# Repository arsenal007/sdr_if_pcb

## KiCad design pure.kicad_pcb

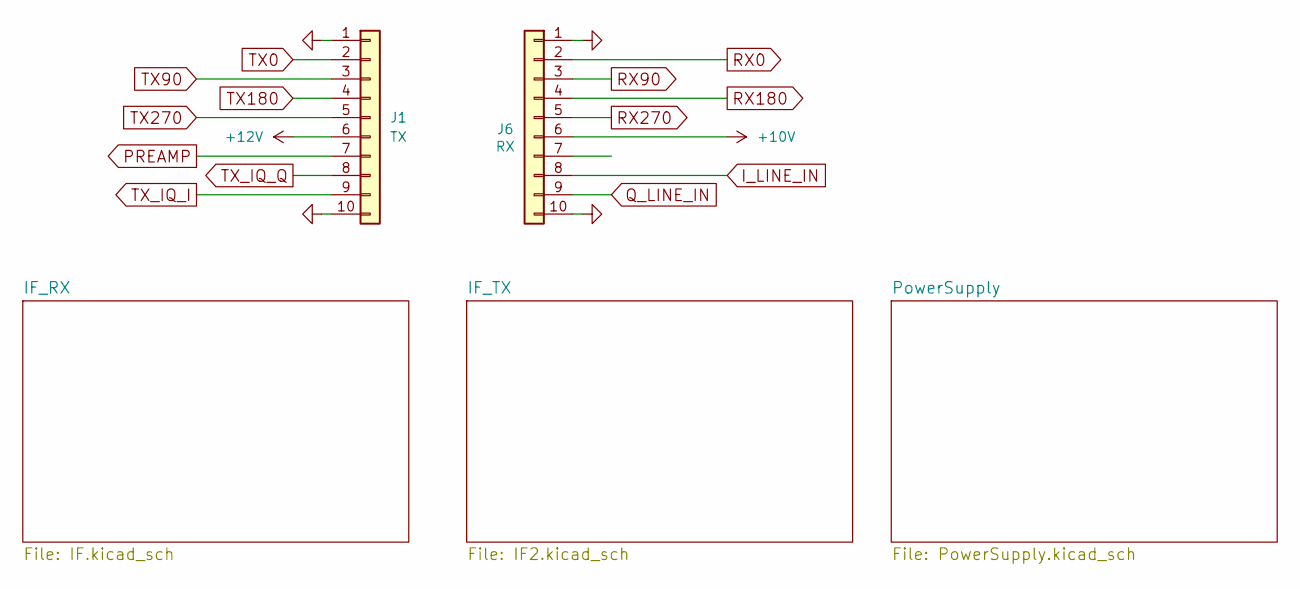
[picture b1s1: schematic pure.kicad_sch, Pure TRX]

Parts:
J1: TX; PinHeader_1x10_P2.54mm_Vertical
J6: RX; PinHeader_1x10_P2.54mm_Vertical

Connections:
+10V: J6.6; also elsewhere on the board
+12V: J1.6; also elsewhere on the board
GND: J1.1, J1.10, J6.1, J6.10; also elsewhere on the board
I_LINE_IN: J6.8; also elsewhere on the board
PREAMP: J1.7; also elsewhere on the board
Q_LINE_IN: J6.9; also elsewhere on the board
RX0: J6.2; also elsewhere on the board
RX90: J6.3; also elsewhere on the board
RX180: J6.4; also elsewhere on the board
RX270: J6.5; also elsewhere on the board
TX0: J1.2; also elsewhere on the board
TX90: J1.3; also elsewhere on the board
TX180: J1.4; also elsewhere on the board
TX270: J1.5; also elsewhere on the board
TX_IQ_I: J1.9; also elsewhere on the board
TX_IQ_Q: J1.8; also elsewhere on the board

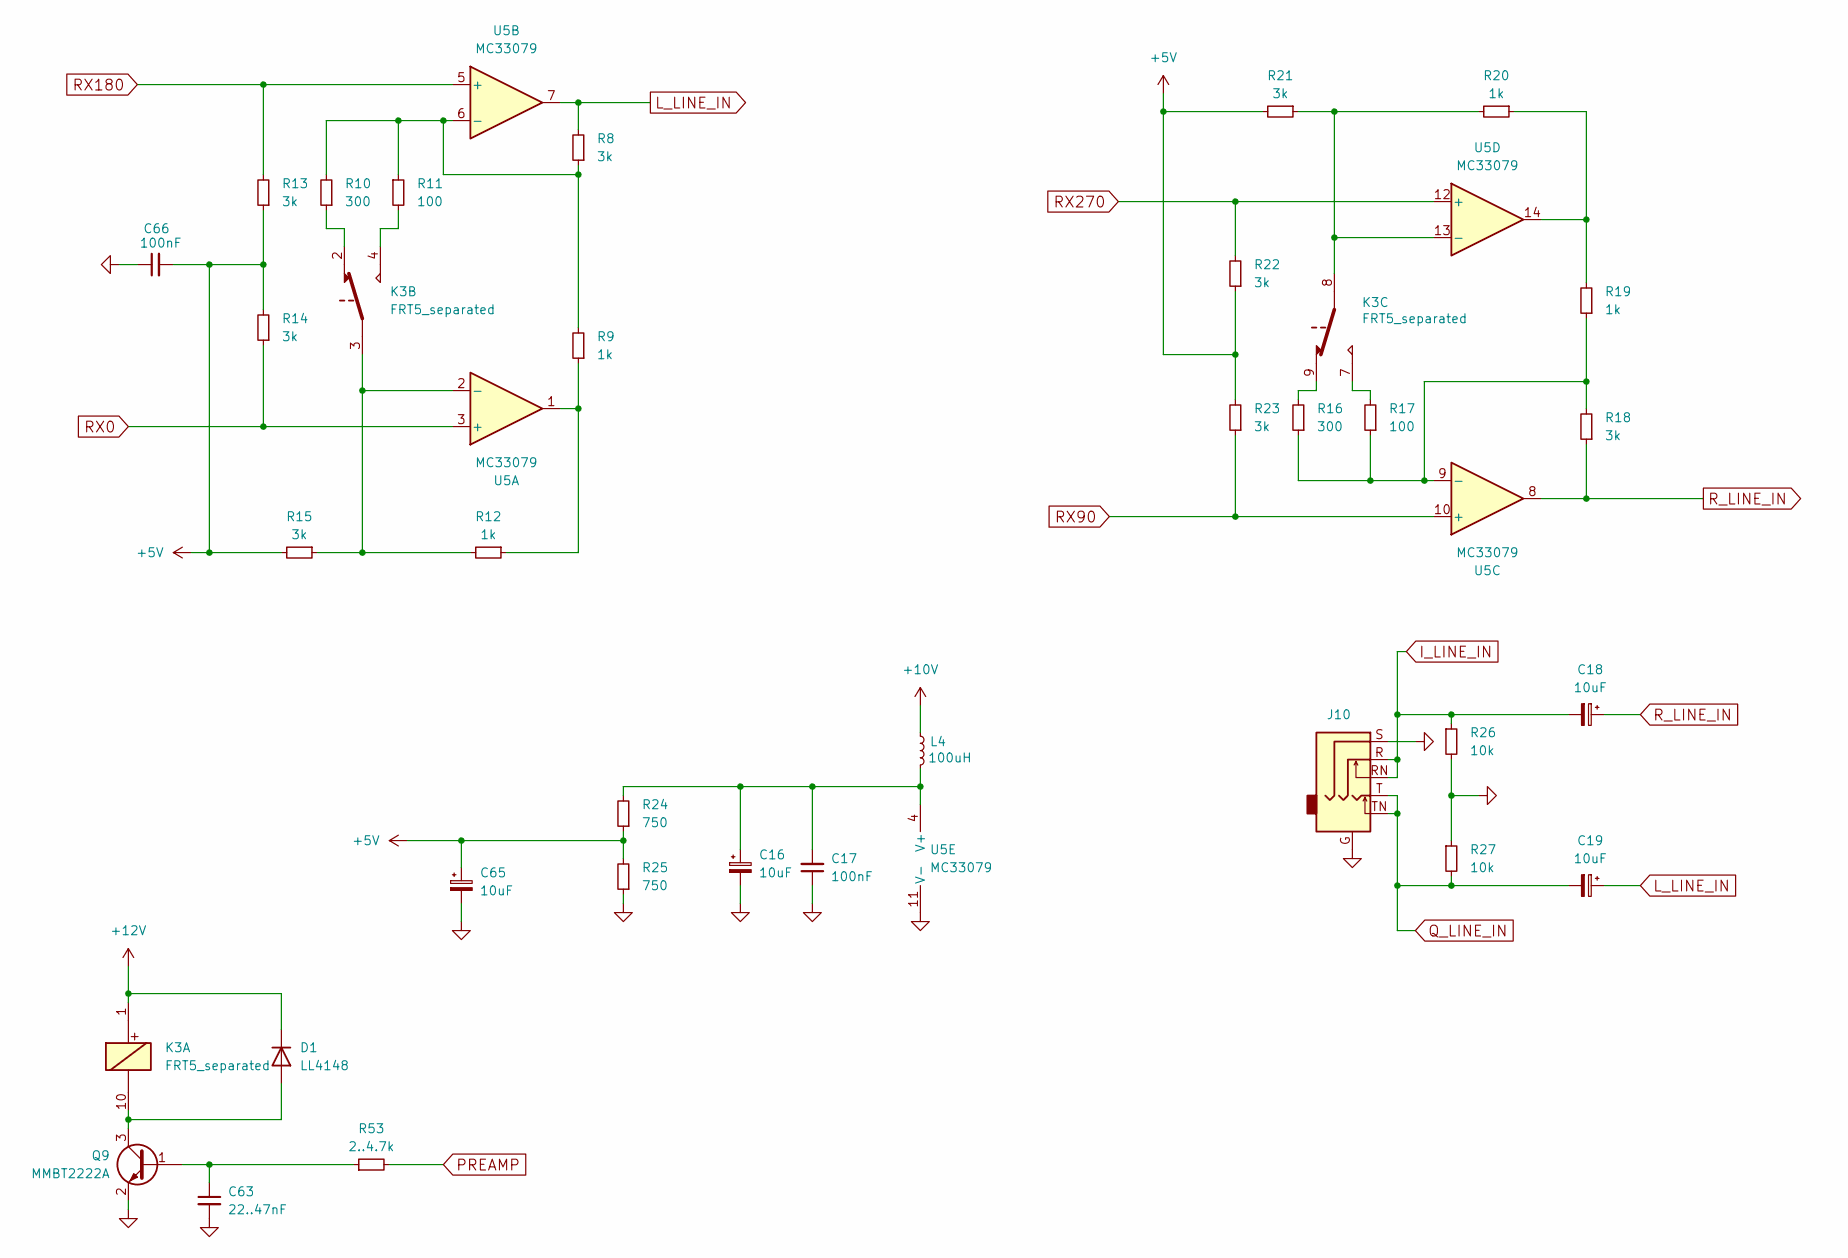
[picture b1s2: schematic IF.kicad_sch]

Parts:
C16, C18, C19, C65: 10uF; CP_EIA-3216-18_Kemet-A_Pad1.58x1.35mm_HandSolder; JLCPCB C123294
C17, C66: 100nF; C_1206_0603; JLCPCB C14663
C63: 22..47nF; C_1206_0603
D1: LL4148; D_MiniMELF
J10: AudioJack3_Ground_SwitchTR; Jack_3.5mm_CUI_SJ1-3525N_Horizontal
K3: FRT5_separated; Relay_DPDT_FRT5
L4: 100uH; L_Axial_L5.3mm_D2.2mm_P10.16mm_Horizontal_Vishay_IM-1; JLCPCB C394100
Q9: MMBT2222A; SOT-23
R8, R13, R14, R15, R18, R21, R22, R23: 3k; R_0603_1608Metric_Pad0.98x0.95mm_HandSolder; JLCPCB C4211
R9, R12, R19, R20: 1k; R_0603_1608Metric_Pad0.98x0.95mm_HandSolder; JLCPCB C21190
R10, R16: 300; R_0603_1608Metric_Pad0.98x0.95mm_HandSolder; JLCPCB C23025
R11, R17: 100; R_0603_1608Metric_Pad0.98x0.95mm_HandSolder; JLCPCB C22775
R24, R25: 750; R_1206_0603; JLCPCB C23241
R26, R27: 10k; R_0603_1608Metric_Pad0.98x0.95mm_HandSolder; JLCPCB C25804
R53: 2..4.7k; R_1206_0603
U5: MC33079; SOIC-14_3.9x8.7mm_P1.27mm

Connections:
+5V: C65.1, C66.2, R13.1, R14.2, R15.2, R21.2, R22.1, R23.2, R24.1, R25.2; also elsewhere on the board
+10V: L4.1; also elsewhere on the board
+12V: D1.1 (K), K3.1; also elsewhere on the board
GND: C16.2, C17.1, C63.2, C65.2, C66.1, J10.G, J10.S, Q9.2 (E), R25.1, R26.2, R27.1, U5.11 (V-); also elsewhere on the board
I_LINE_IN: C18.2, J10.R, J10.RN, R26.1; also elsewhere on the board
L_LINE_IN: C19.1, R8.2, U5.7
unnamed: D1.2 (A), K3.10, Q9.3 (C)
unnamed: K3.2, R10.1
unnamed: K3.4, R11.2
unnamed: K3.7, R17.2
unnamed: K3.9, R16.2
unnamed: C63.1, Q9.1 (B), R53.1
unnamed: R9.1, R12.1, U5.1
unnamed: R19.2, R20.1, U5.14
unnamed: K3.3, R12.2, R15.1, U5.2 (-)
unnamed: R8.1, R9.2, R10.2, R11.1, U5.6 (-)
unnamed: R16.1, R17.1, R18.2, R19.1, U5.9 (-)
unnamed: K3.8, R20.2, R21.1, U5.13 (-)
unnamed: C16.1, C17.2, L4.2, R24.2, U5.4 (V+)
PREAMP: R53.2; also elsewhere on the board
Q_LINE_IN: C19.2, J10.T, J10.TN, R27.2; also elsewhere on the board
RX0: R14.1, U5.3 (+); also elsewhere on the board
RX90: R23.1, U5.10 (+); also elsewhere on the board
RX180: R13.2, U5.5 (+); also elsewhere on the board
RX270: R22.2, U5.12 (+); also elsewhere on the board
R_LINE_IN: C18.1, R18.1, U5.8

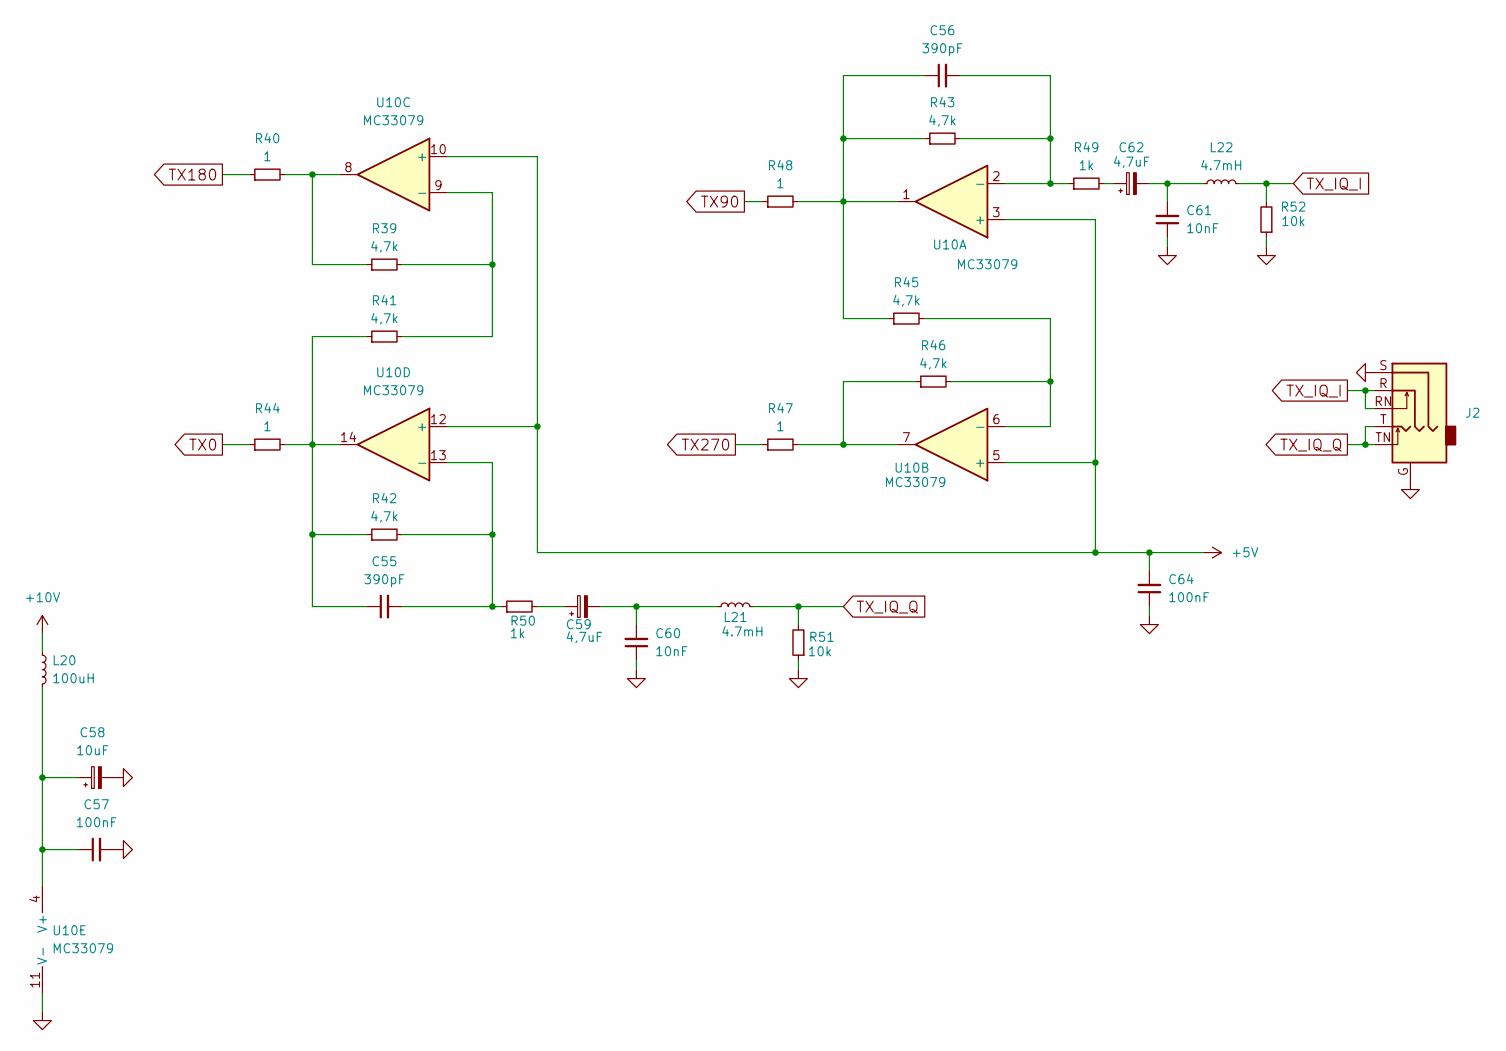
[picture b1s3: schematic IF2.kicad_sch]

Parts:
C55, C56: 390pF; C_0603_1608Metric_Pad1.08x0.95mm_HandSolder
C57, C64: 100nF; C_1206_0603
C58: 10uF; CP_EIA-3216-18_Kemet-A_Pad1.58x1.35mm_HandSolder
C59, C62: 4,7uF; CP_EIA-3216-18_Kemet-A_Pad1.58x1.35mm_HandSolder
C60, C61: 10nF; C_0603_1608Metric_Pad1.08x0.95mm_HandSolder
J2: AudioJack3_Ground_SwitchTR; Jack_3.5mm_CUI_SJ1-3525N_Horizontal
L20: 100uH; L_Axial_L5.3mm_D2.2mm_P10.16mm_Horizontal_Vishay_IM-1
L21, L22: 4.7mH; L_Axial_L5.3mm_D2.2mm_P10.16mm_Horizontal_Vishay_IM-1
R39, R41, R42, R43, R45, R46: 4,7k; R_0603_1608Metric_Pad0.98x0.95mm_HandSolder
R40, R44, R47, R48: 1; R_1206_0603
R49, R50: 1k; R_0603_1608Metric_Pad0.98x0.95mm_HandSolder
R51, R52: 10k; R_0603_1608Metric_Pad0.98x0.95mm_HandSolder
U10: MC33079; SOIC-14_3.9x8.7mm_P1.27mm

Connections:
+5V: C64.2, U10.3 (+), U10.5 (+), U10.10 (+), U10.12 (+); also elsewhere on the board
+10V: L20.1; also elsewhere on the board
GND: C57.2, C58.2, C60.1, C61.1, C64.1, J2.G, J2.S, R51.1, R52.1, U10.11 (V-); also elsewhere on the board
unnamed: C55.1, R41.1, R42.1, R44.2, U10.14
unnamed: C56.1, R43.1, R45.1, R48.2, U10.1
unnamed: C59.1, R50.2
unnamed: C59.2, C60.2, L21.1
unnamed: C61.2, C62.2, L22.1
unnamed: C62.1, R49.2
unnamed: R39.1, R40.2, U10.8
unnamed: R46.1, R47.2, U10.7
unnamed: C56.2, R43.2, R49.1, U10.2 (-)
unnamed: R45.2, R46.2, U10.6 (-)
unnamed: R39.2, R41.2, U10.9 (-)
unnamed: C55.2, R42.2, R50.1, U10.13 (-)
unnamed: C57.1, C58.1, L20.2, U10.4 (V+)
TX0: R44.1; also elsewhere on the board
TX90: R48.1; also elsewhere on the board
TX180: R40.1; also elsewhere on the board
TX270: R47.1; also elsewhere on the board
TX_IQ_I: J2.R, J2.RN, L22.2, R52.2; also elsewhere on the board
TX_IQ_Q: J2.T, J2.TN, L21.2, R51.2; also elsewhere on the board

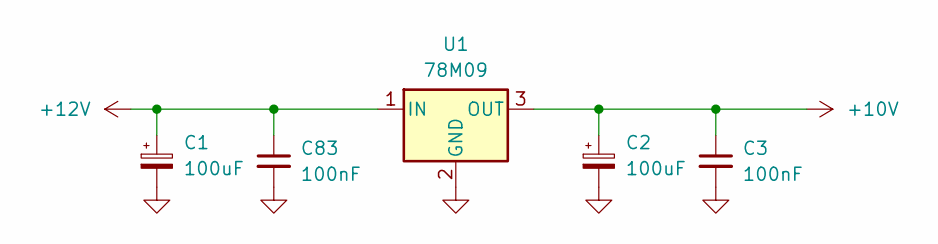
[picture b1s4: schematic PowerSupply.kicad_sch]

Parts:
C1, C2: 100uF; CP_EIA-7343-15_Kemet-W_Pad2.25x2.55mm_HandSolder
C3, C83: 100nF; C_1206_0603
U1: 78M09; TO-252-2

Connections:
+10V: C2.1, C3.1, U1.3 (OUT); also elsewhere on the board
+12V: C1.1, C83.1, U1.1 (IN); also elsewhere on the board
GND: C1.2, C2.2, C3.2, C83.2, U1.2 (GND); also elsewhere on the board

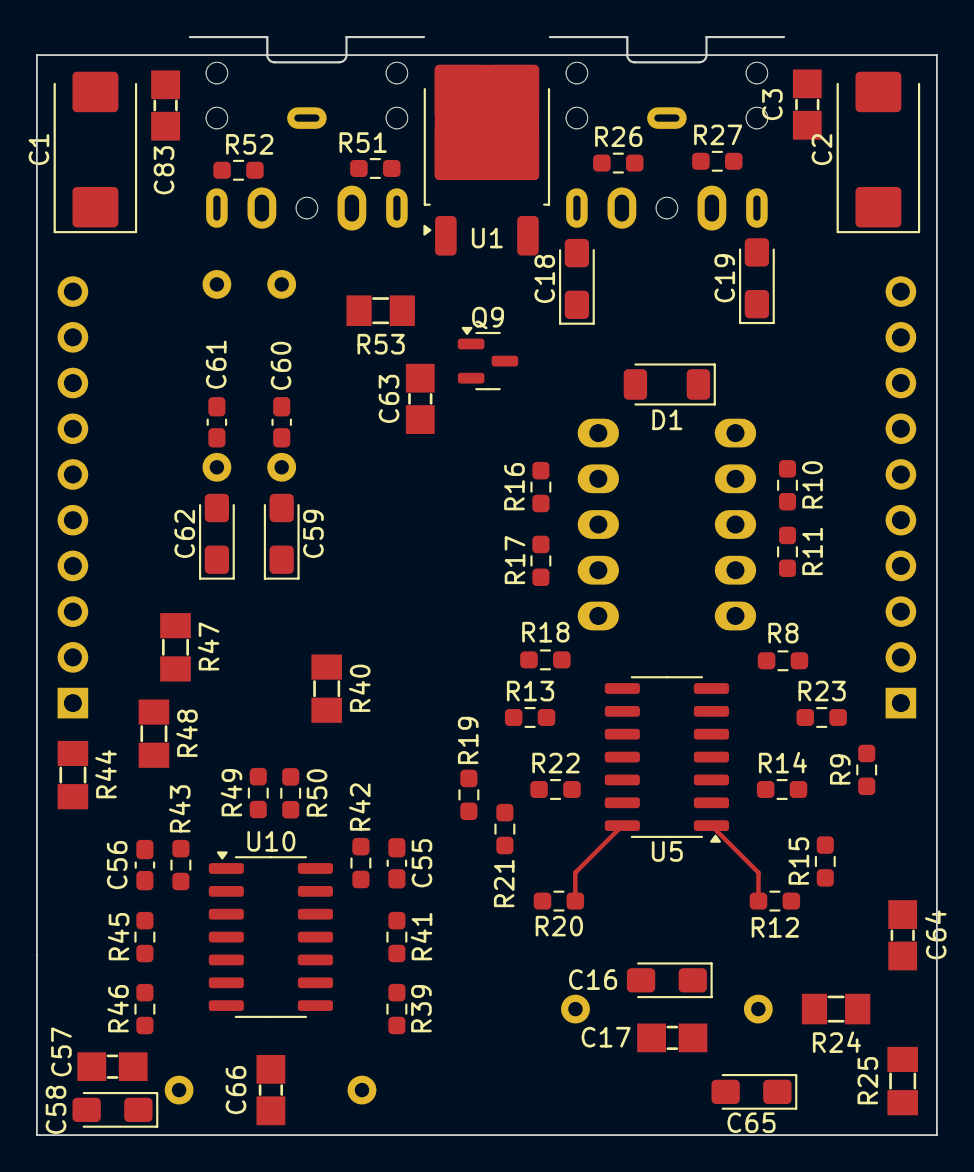
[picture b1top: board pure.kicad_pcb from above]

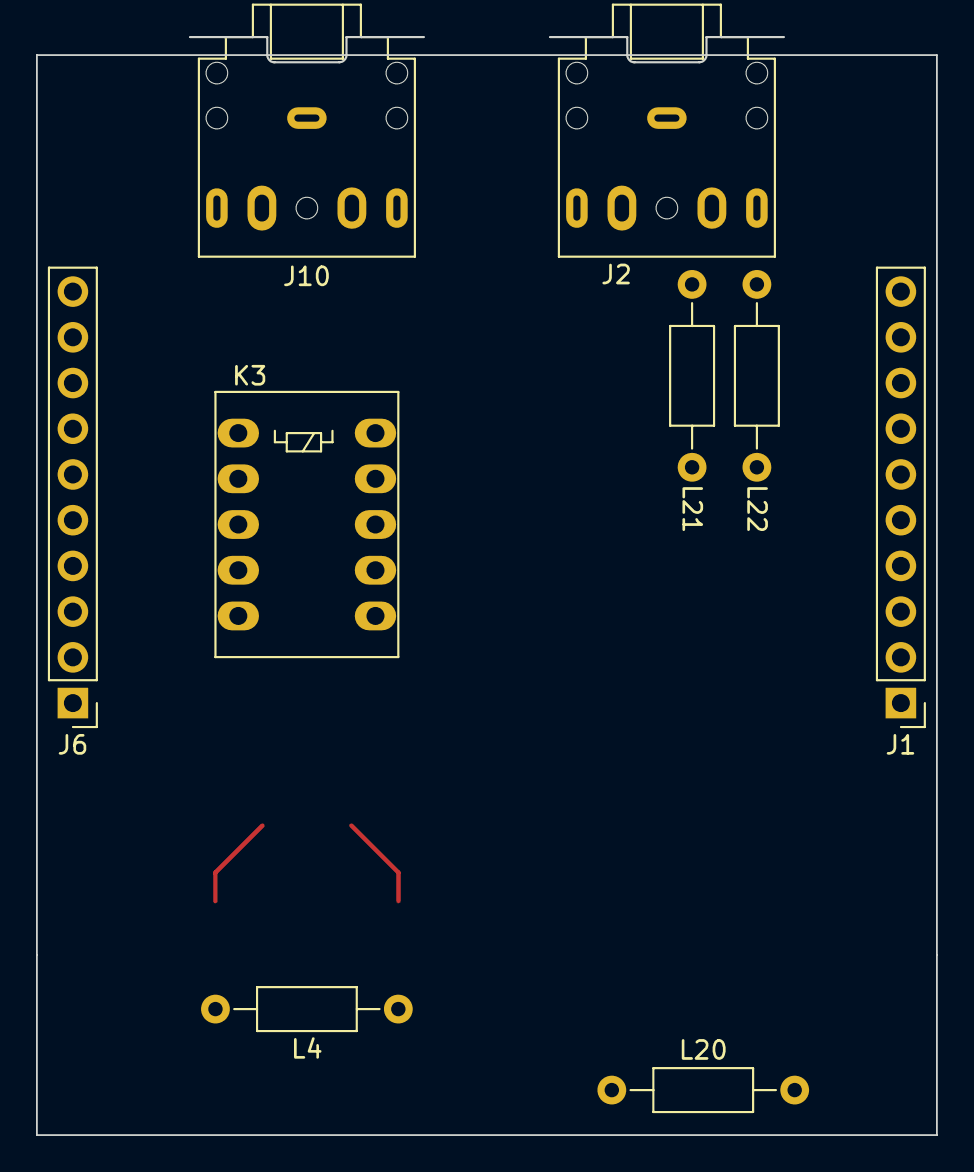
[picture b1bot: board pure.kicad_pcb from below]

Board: 2 copper layers, 50.0 x 61.0 mm, 69 parts (9 on the bottom side), 45 nets.

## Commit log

2019-09-13 test printf, ssd1306
2024-05-20 add whole module PCB
2024-05-20 add SDR IF module schematic symbol
2024-05-20 rename pure to SDR_IF
